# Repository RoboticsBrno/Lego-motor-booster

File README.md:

# lego-motor-booster
Booster for lego motors by @RoboticsBrno

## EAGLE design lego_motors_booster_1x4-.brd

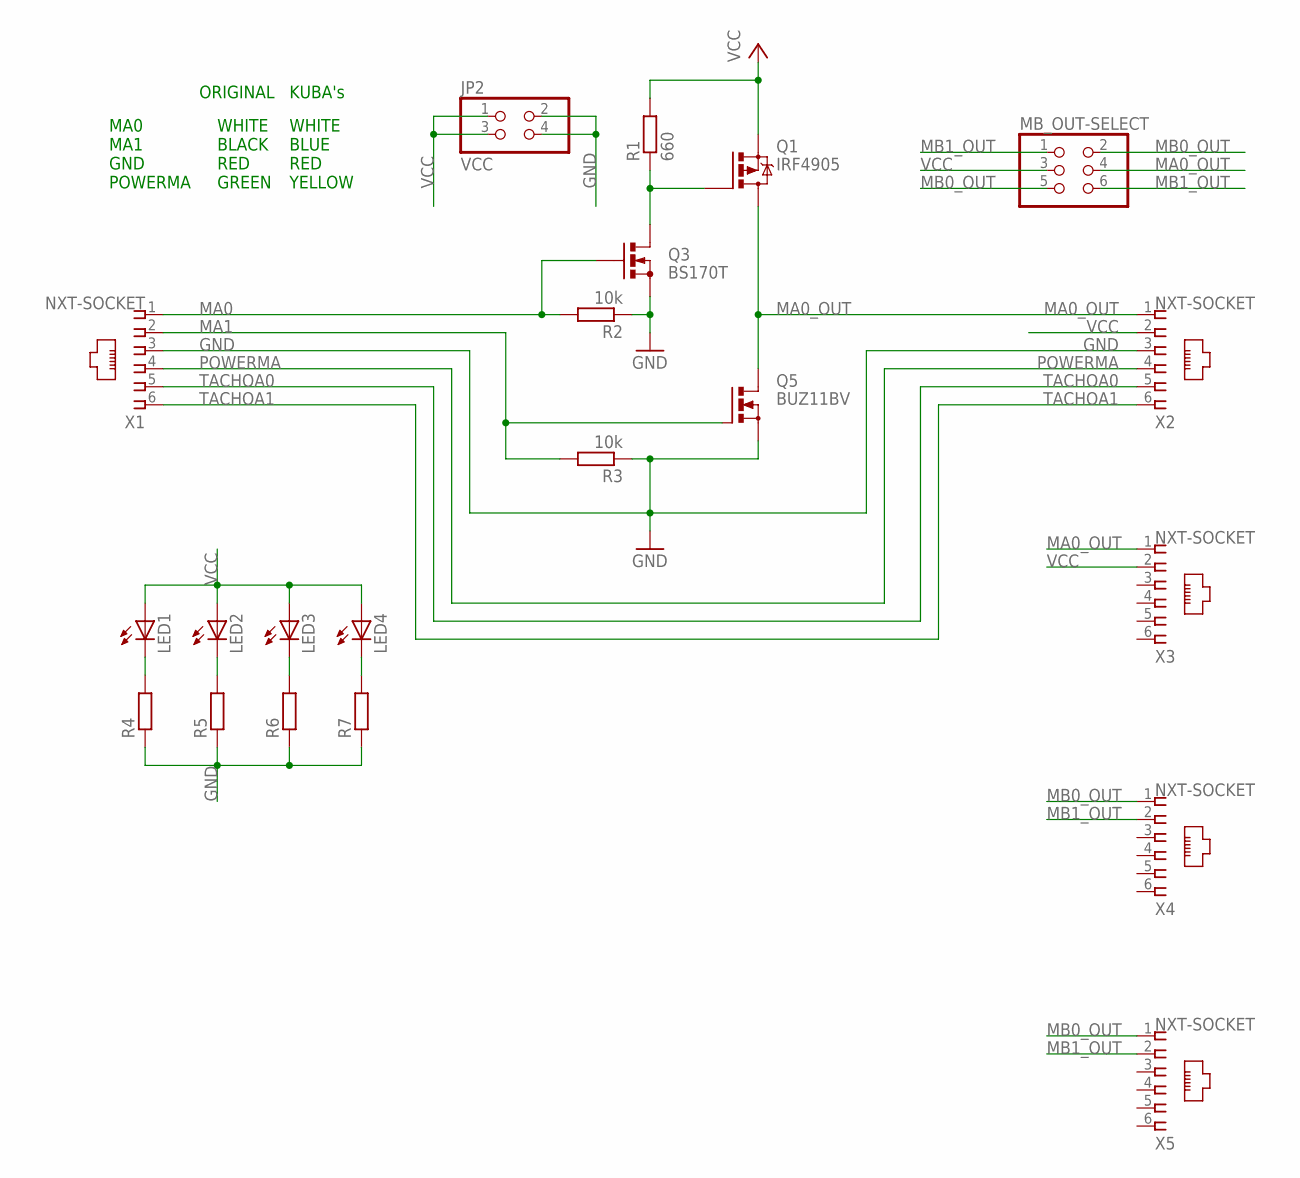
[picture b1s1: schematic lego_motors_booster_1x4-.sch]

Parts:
JP2: VCC; 2X02
LED1, LED2, LED3, LED4: LEDSML0603; SML0603
MB_OUT-SELECT: PINHD-2X3; 2X03
Q1: IRF4905; TO220BV
Q3: BS170T; SOT54E
Q5: BUZ11BV; TO220BV
R1: 660; 0204/7
R2, R3: 10k; 0204/7
R4, R5, R6, R7: R-EU_R0603; R0603
X1, X2, X3, X4, X5: NXT-SOCKET

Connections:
GND: JP2.2, JP2.4, Q3.S, Q5.S, R2.1, R3.1, R4.1, R5.1, R6.1, R7.1, X1.3, X2.3
MA0: Q3.G, R2.2, X1.1
MA0_OUT: MB_OUT-SELECT.4, Q1.D, Q5.D, X2.1, X3.1
MA1: Q5.G, R3.2, X1.2
MB0_OUT: MB_OUT-SELECT.2, MB_OUT-SELECT.5, X4.1, X5.1
MB1_OUT: MB_OUT-SELECT.1, MB_OUT-SELECT.6, X4.2, X5.2
unnamed: Q1.G, Q3.D, R1.1
unnamed: LED1.C, R4.2
unnamed: LED2.C, R5.2
unnamed: LED3.C, R6.2
unnamed: LED4.C, R7.2
POWERMA: X1.4, X2.4
TACHOA0: X1.5, X2.5
TACHOA1: X1.6, X2.6
VCC: JP2.1, JP2.3, LED1.A, LED2.A, LED3.A, LED4.A, MB_OUT-SELECT.3, Q1.S, R1.2, X2.2, X3.2

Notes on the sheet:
WHITE BLUE RED YELLOW
WHITE BLACK RED GREEN
ORIGINAL
KUBA's
MA0 MA1 GND POWERMA

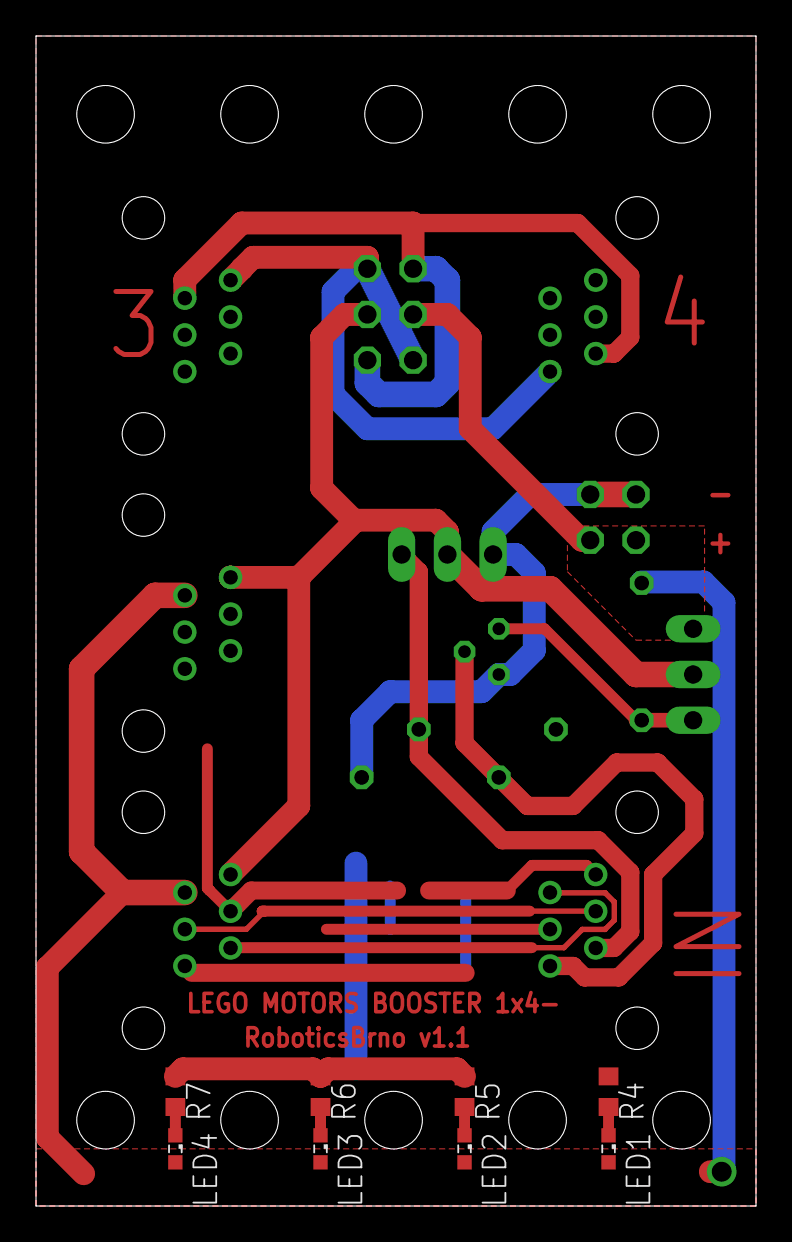
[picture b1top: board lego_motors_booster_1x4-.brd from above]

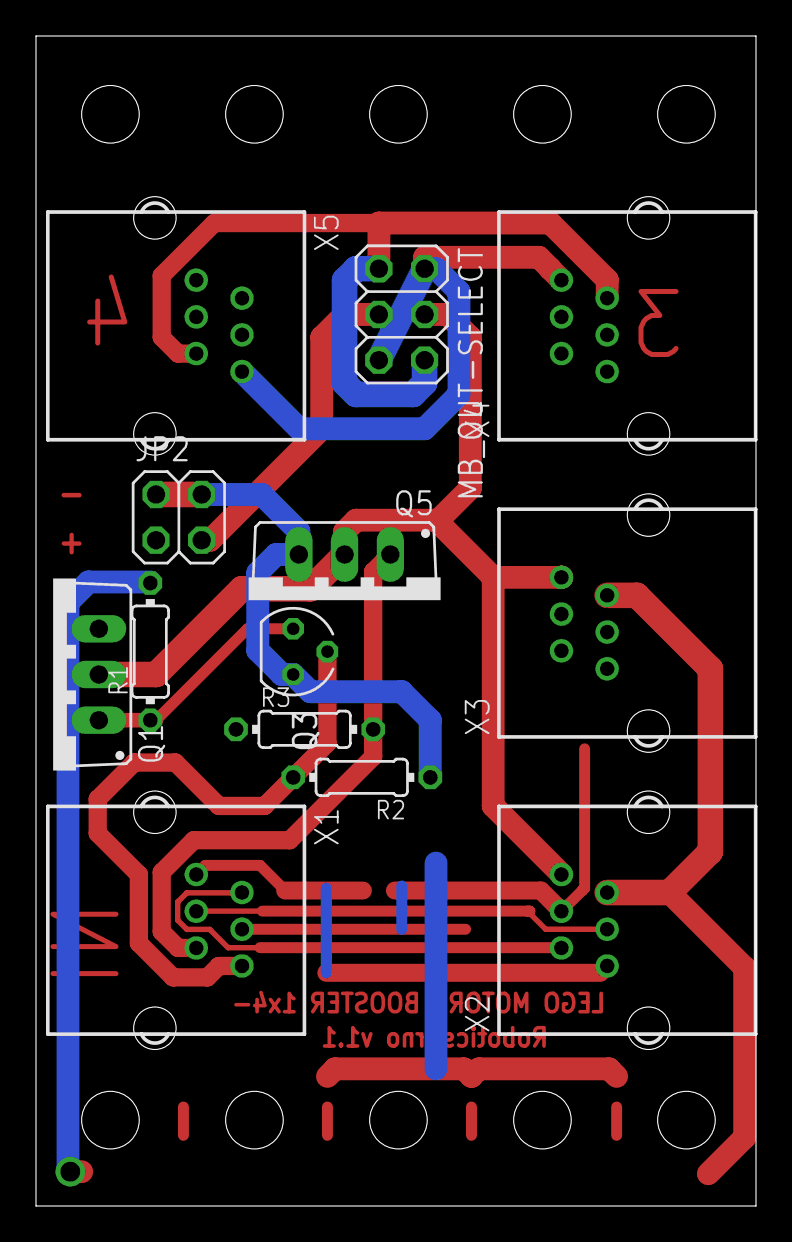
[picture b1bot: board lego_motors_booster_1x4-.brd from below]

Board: 2 copper layers, 40.0 x 65.0 mm, 21 parts (13 on the bottom side), 15 nets.

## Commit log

2017-02-08 lego_motors_booster_1x4-: first version with all features (4 motors, reverse setting for motor 3 and 4, turn on GND, ...)
2017-02-08 lego_motors_booster_1x4-: second version with different layout => all other things same
2017-02-09 mirrored + maybe some minor improvements
2017-02-09 Added tag HW v1.1 for changeset 9d4f73838c2b
2018-07-22 Add eagle GitIgnore
